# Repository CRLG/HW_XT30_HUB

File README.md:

# HW_XT30_HUB
Hub pour connecteurs XT30.
Projet Kicad.

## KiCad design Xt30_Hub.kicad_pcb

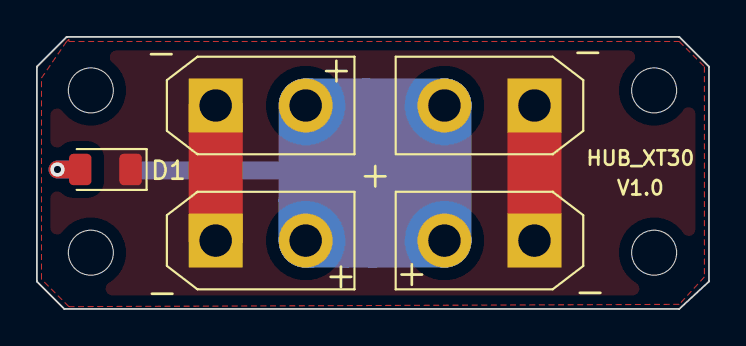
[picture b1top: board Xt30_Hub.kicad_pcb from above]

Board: 2 copper layers, 37.3 x 15.1 mm, 10 parts (1 on the bottom side), 3 nets.

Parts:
D1: LED; D_1206_3216Metric
H1, H2, H3, H4: MountingHole; MountingHole_2.5mm
J1: Conn_XT30M; AMASS_XT30UPB-M_1x02_P5.0mm_Vertical
J2, J3, J4: Conn_XT30F; AMASS_XT30UPB-F_1x02_P5.0mm_Vertical
R1: R; R_1206_3216Metric

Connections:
/MOINS: D1.1, J1.1, J2.1, J3.1, J4.1
/PLUS: J1.2, J2.2, J3.2, J4.2, R1.1
unnamed: D1.2, R1.2

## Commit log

2019-09-15 Mise à jour du readme
2019-09-15 Ajout du sous-module KICAD_LIB au projet
2019-09-15 Version initiale du projet
